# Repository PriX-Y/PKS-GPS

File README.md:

# **PKS-GPS**

GPS module with custome PCB and Case

I made becuse i need gps in my GPS to my project but i dont wanna put this in **BIG Project**
there is not anntena becuse for now i dont need. I made this i track road and speed
for that moment i no need code for it
# there is visual in a case:

and closed

im not use screaw becuse its  small ( 30mm ) and i use hot glue to close that

# **Parts**

** Is base on uBLOK MAX-M10S gps mcu its cheap but very good ** 

** i give to it 2.54mm pin conector becuse i need something to connect i think its a little to big for this project but work , work **

 ** red diod what i have for free from my arduino **

** capacitors and resistors is smd yeah but in 805 case and i wanna teach how to sold smd becuse is harder then tht **

this connector for connector its cheap and good :)

that all parts

# Programs

kicad(pcb)

google dosc (bom)

# there is BOM 

**Parts from kicad:**

**Parts to buy BOM**

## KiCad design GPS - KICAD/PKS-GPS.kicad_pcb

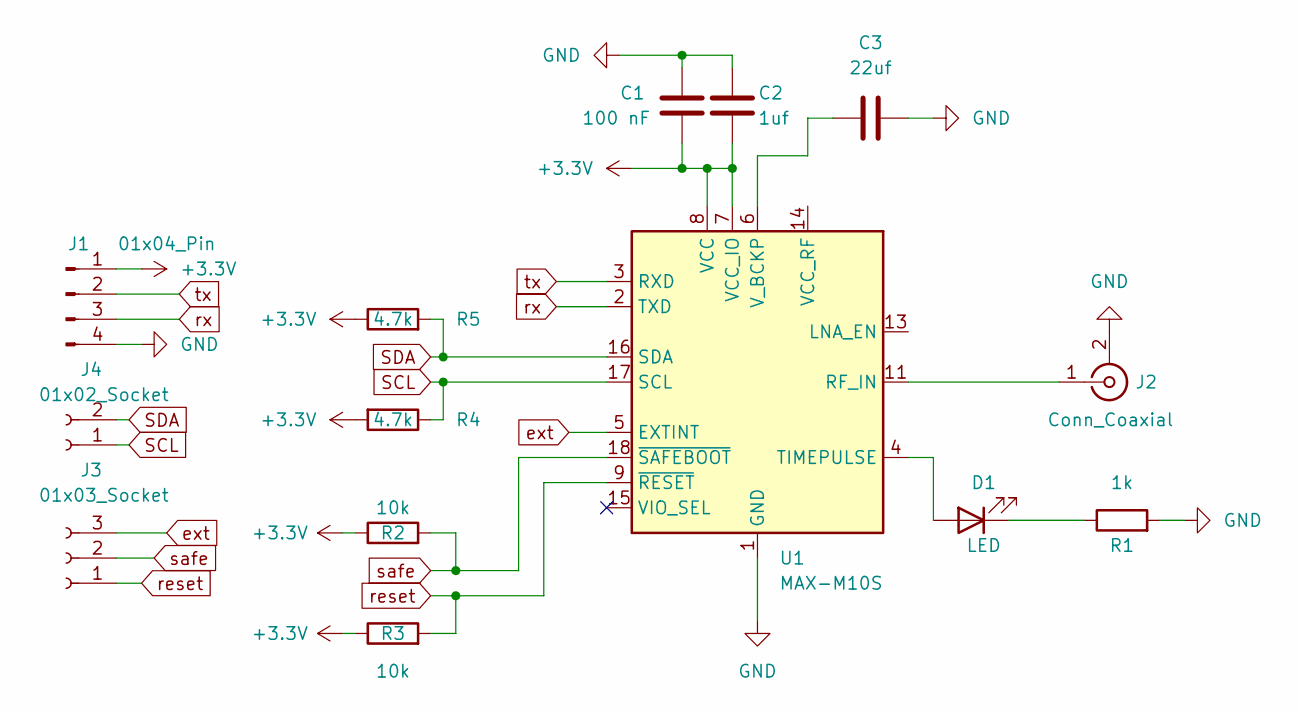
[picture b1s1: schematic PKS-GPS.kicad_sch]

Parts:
C1: 100 nF; C_0805_2012Metric_Pad1.18x1.45mm_HandSolder
C2: 1uf; C_0805_2012Metric_Pad1.18x1.45mm_HandSolder
C3: 22uf; C_0805_2012Metric_Pad1.18x1.45mm_HandSolder
D1: LED; LED_D3.0mm
J1: 01x04_Pin; PinSocket_1x04_P2.54mm_Horizontal
J2: Conn_Coaxial; MMCX_Molex_73415-0961_Horizontal_1.6mm-PCB
J3: 01x03_Socket; PinSocket_1x03_P2.54mm_Horizontal
J4: 01x02_Socket; PinSocket_1x02_P2.54mm_Horizontal
R1: 1k; R_0805_2012Metric_Pad1.20x1.40mm_HandSolder
R2, R3: 10k; R_0805_2012Metric_Pad1.20x1.40mm_HandSolder
R4, R5: 4.7k; R_0805_2012Metric_Pad1.20x1.40mm_HandSolder
U1: MAX-M10S; ublox_MAX

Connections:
+3.3V: C1.2, C2.2, J1.1, R2.1, R3.1, R4.2, R5.1, U1.7 (VCC_IO), U1.8 (VCC)
GND: C1.1, C2.1, C3.1, J1.4, J2.2 (Ext), R1.2, U1.1 (GND), U1.10 (GND), U1.12 (GND)
unnamed: D1.2 (A), U1.4 (TIMEPULSE)
unnamed: D1.1 (K), R1.1
unnamed: J2.1 (In), U1.11 (RF_IN)
unnamed: C3.2, U1.6 (V_BCKP)
SCL: J4.1, R4.1, U1.17 (SCL)
SDA: J4.2, R5.2, U1.16 (SDA)
ext: J3.3, U1.5 (EXTINT)
reset: J3.1, R3.2, U1.9 (~RESET)
rx: J1.3, U1.2 (TXD)
safe: J3.2, R2.2, U1.18 (~SAFEBOOT)
tx: J1.2, U1.3 (RXD)

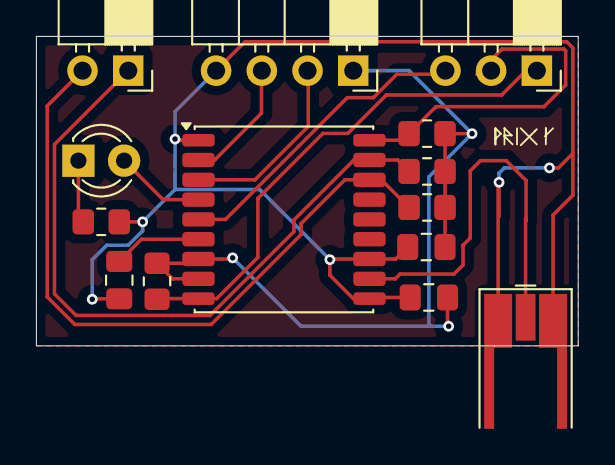
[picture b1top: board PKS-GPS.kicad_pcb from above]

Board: 2 copper layers, 30.1 x 17.2 mm, 14 parts (0 on the bottom side), 13 nets.

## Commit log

2026-03-31 Improve README formatting and content
    Updated README to enhance formatting and clarity.
2026-04-01 Fix typos and improve README clarity
    Corrected spelling and grammar errors in the README.
2026-04-01 Fix typos and enhance README clarity
    Corrected typos and improved clarity in the README.
